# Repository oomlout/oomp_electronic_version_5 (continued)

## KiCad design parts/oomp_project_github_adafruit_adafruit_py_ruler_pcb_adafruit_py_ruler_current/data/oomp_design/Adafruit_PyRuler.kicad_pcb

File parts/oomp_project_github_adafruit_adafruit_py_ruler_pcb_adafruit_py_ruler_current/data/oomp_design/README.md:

# OOMP KiCad design copy

Open `Adafruit_PyRuler.kicad_pro` (or the `.kicad_pcb` / `.kicad_sch`) in KiCad. Local OOMP libraries are under `libraries/`. Original inputs are preserved in [../original/](../original/).

Only verified unchanged installed KiCad defaults were renamed. Modified, custom, unmatched and unavailable items remain unchanged. Soldering variants are never swapped during conversion. Existing pad coordinates, nets and UUIDs are preserved.

See [conversion_report.yaml](conversion_report.yaml) for every conversion and skip. Copy this directory before editing; regeneration refuses to overwrite edited design files.

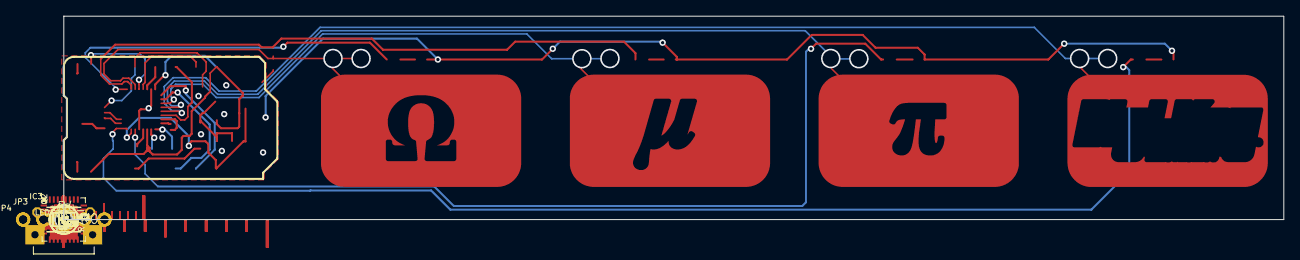
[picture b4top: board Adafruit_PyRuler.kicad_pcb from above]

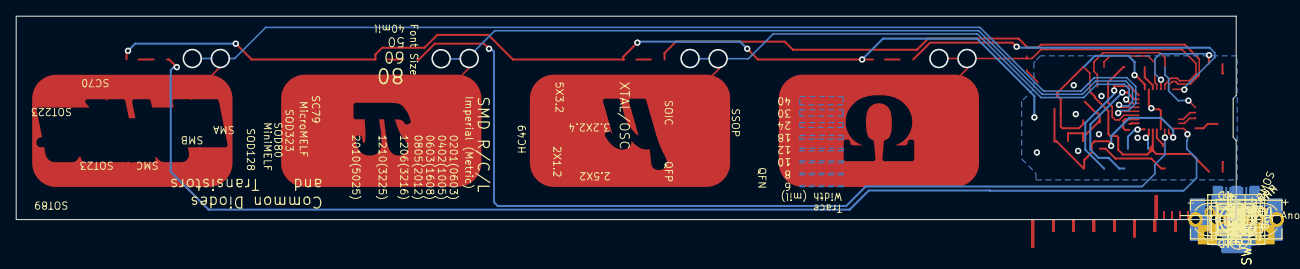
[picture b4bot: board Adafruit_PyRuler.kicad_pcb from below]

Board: 16 copper layers, 152.4 x 25.4 mm, 98 parts (43 on the bottom side), 30 nets.

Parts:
C1, C8: 10uF; 0805-NO
C2, C3: 1uF; 0603-NO
CN1: 4U#20329; 4UCONN_20329_NARROW
D2, D3: SCHOTTKY; SOD-123FL
E$1, E$2, E$3, E$4, E$5, E$6, E$7, E$8, E$9, E$10, E$11, E$12, E$13, E$14, E$15: EDGE-MILLIMETERS
E$16, E$60, E$63: 0201
E$17, E$18, E$19, E$20, E$21, E$22: EDGE-INCHES-TENTH
E$23, E$61: 0402
E$24, E$62: 0603
E$25: 0805
E$26: 1206
E$27: 1210
E$28: 2010
E$31: SOT223
E$32: SOT89
E$33: SOT23-5
E$34: SOT23-3
E$35: SC70
E$36: CRYSTAL-SMD-5X3.2
E$37: CRYSTAL-SMD-3.2X2.5
E$38: CRYSTAL-SMD-2.5X2
E$39: HC49UP
E$40: XTAL-2X1.2
E$41: MICROMELF-R
E$42: SC79_INFINEON
E$43: SMA-DIODE
E$44: SMB-DIODE
E$45: SMC
E$47: SOD-128
E$48: SOD-323
E$49: SOD80C
E$50: NMOS-SYMB
E$51: PMOS-SYMB
E$52: DIODE-SYMB
E$53: LED-GUIDE
E$54: NPN-SYMB
E$55: QFN-24
E$56: TSSOP16
E$57: SO08
E$58: TQFP32-5MM
E$59: PNP-SYMB
IC3: ATSAMD21E; QFN32_5MM
JP3, JP4: 1X05_ROUND_70
L0, L2: red; CHIPLED_0603_NOOUTLINE
L1: yellow; CHIPLED_0603_NOOUTLINE
L3: blue; CHIPLED_0603_NOOUTLINE
L4: green; CHIPLED_0603_NOOUTLINE
LED1: AP102-2020; APA102_2020
PWR0: green; CHIPLED_0603_NOOUTLINE
Q2: reset; BTN_KMR2_4.6X2.8
R1, R2, R3: 2.2K; 0603-NO
R4, R5, R6: 10K; 0603-NO
R7: 2M; 0603-NO
SWC0: TPB1,27; B1,27
SWD0: TPB1,27; B1,27
U1: AP2112K-3.3; SOT23-5
U$1, U$6: FIDUCIAL_1MM
U$2: PYRULER_BOTTOM
U$7: PCBFEAT-REV-040
U$8, U$9: MOUNTINGHOLE2.0; MOUNTINGHOLE_2.0_PLATED
U$14: PYRULER_TOP
U$20: TRINKET_M0_TOP
UNK_HOLE_0: dummyfp0
UNK_HOLE_1: dummyfp1

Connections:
3.3V: C2.1, C8.1, IC3.9, IC3.30, JP4.1, LED1.3, R4.2, U1.5
CAP0: IC3.14, R7.1
D0_A4_PA08_SDA: IC3.11, JP4.4
D1_A0_PA02: IC3.3, JP4.3
D2_A1_PA09_SCL_MISO: IC3.12, JP4.2
D3_A3_PA07_RXD_SCK: IC3.8, JP3.4
D4_A2_PA06_TXD_MOSI: IC3.7, JP3.3
D+: CN1.D+, IC3.24
D-: CN1.D-, IC3.23
DOTSTAR_CLOCK: IC3.2, LED1.5
DOTSTAR_DATA: IC3.1, LED1.6
GND: C1.2, C2.2, C3.2, C8.2, CN1.BASE@1, CN1.BASE@2, CN1.GND, CN1.SPRT@1, CN1.SPRT@2, CN1.SPRT@3, CN1.SPRT@4, IC3.10, IC3.28, IC3.33, JP3.2, L0.C, L1.C, L2.C, L3.C, L4.C, LED1.4, PWR0.C, Q2.B, Q2.B', R7.2, U1.2
LED: IC3.13, R1.2
LED4: IC3.16, R3.2
LED5: IC3.15, R2.2
LED6: IC3.27, R6.2
LED7: IC3.25, R5.2
unnamed: L0.A, R1.1
unnamed: IC3.31, SWC0.TP
unnamed: IC3.32, SWD0.TP
unnamed: PWR0.A, R4.1
unnamed: L1.A, R2.1
unnamed: L2.A, R3.1
unnamed: L4.A, R6.1
unnamed: L3.A, R5.1
VBAT: D3.A, JP3.1
VBUS: CN1.VBUS, D2.A, JP4.5
VDDCORE: C3.1, IC3.29
VOUT: C1.1, D2.C, D3.C, U1.1, U1.3
~RESET: IC3.26, JP3.5, Q2.A, Q2.A'

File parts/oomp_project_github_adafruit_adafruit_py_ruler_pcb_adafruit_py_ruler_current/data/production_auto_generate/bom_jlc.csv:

Comment,Designator,Footprint,LCSC Part #
,"E$16,E$60,E$63",Adafruit_PyRuler-import-fps:0201,
,"E$23,E$61",Adafruit_PyRuler-import-fps:0402,
,"E$24,E$62",Adafruit_PyRuler-import-fps:0603,
,E$25,Adafruit_PyRuler-import-fps:0805,
,E$26,Adafruit_PyRuler-import-fps:1206,
,E$27,Adafruit_PyRuler-import-fps:1210,
,"JP3,JP4",Adafruit_PyRuler-import-fps:1X05_ROUND_70,C42431835
,E$28,Adafruit_PyRuler-import-fps:2010,
,E$38,Adafruit_PyRuler-import-fps:CRYSTAL-SMD-2.5X2,
,E$37,Adafruit_PyRuler-import-fps:CRYSTAL-SMD-3.2X2.5,
,E$36,Adafruit_PyRuler-import-fps:CRYSTAL-SMD-5X3.2,
,E$52,Adafruit_PyRuler-import-fps:DIODE-SYMB,
,"E$17,E$18,E$19,E$20,E$21,E$22",Adafruit_PyRuler-import-fps:EDGE-INCHES-TENTH,
,"E$1,E$2,E$3,E$4,E$5,E$6,E$7,E$8,E$9,E$10,E$11,E$12,E$13,E$14,E$15",Adafruit_PyRuler-import-fps:EDGE-MILLIMETERS,
,E$39,Adafruit_PyRuler-import-fps:HC49UP,
,E$53,Adafruit_PyRuler-import-fps:LED-GUIDE,
,E$41,Adafruit_PyRuler-import-fps:MICROMELF-R,
,E$50,Adafruit_PyRuler-import-fps:NMOS-SYMB,
,E$54,Adafruit_PyRuler-import-fps:NPN-SYMB,
,U$7,Adafruit_PyRuler-import-fps:PCBFEAT-REV-040,
,E$51,Adafruit_PyRuler-import-fps:PMOS-SYMB,
,E$59,Adafruit_PyRuler-import-fps:PNP-SYMB,
,U$2,Adafruit_PyRuler-import-fps:PYRULER_BOTTOM,
,U$14,Adafruit_PyRuler-import-fps:PYRULER_TOP,
,E$55,Adafruit_PyRuler-import-fps:QFN-24,
,E$35,Adafruit_PyRuler-import-fps:SC70,
,E$42,Adafruit_PyRuler-import-fps:SC79_INFINEON,
,E$43,Adafruit_PyRuler-import-fps:SMA-DIODE,
,E$44,Adafruit_PyRuler-import-fps:SMB-DIODE,
,E$45,Adafruit_PyRuler-import-fps:SMC,
,E$57,Adafruit_PyRuler-import-fps:SO08,
,E$47,Adafruit_PyRuler-import-fps:SOD-128,
,E$48,Adafruit_PyRuler-import-fps:SOD-323,
,E$49,Adafruit_PyRuler-import-fps:SOD80C,
,E$31,Adafruit_PyRuler-import-fps:SOT223,
,E$34,Adafruit_PyRuler-import-fps:SOT23-3,
,E$33,Adafruit_PyRuler-import-fps:SOT23-5,
,E$32,Adafruit_PyRuler-import-fps:SOT89,
,E$58,Adafruit_PyRuler-import-fps:TQFP32-5MM,
,U$20,Adafruit_PyRuler-import-fps:TRINKET_M0_TOP,
,E$56,Adafruit_PyRuler-import-fps:TSSOP16,
,E$40,Adafruit_PyRuler-import-fps:XTAL-2X1.2,
10K,"R4,R5,R6",Adafruit_PyRuler-import-fps:0603-NO,C98220
10uF,"C1,C8",Adafruit_PyRuler-import-fps:0805-NO,
1uF,"C2,C3",Adafruit_PyRuler-import-fps:0603-NO,C5673
2.2K,"R1,R2,R3",Adafruit_PyRuler-import-fps:0603-NO,C4190
2M,R7,Adafruit_PyRuler-import-fps:0603-NO,
4U#20329,CN1,Adafruit_PyRuler-import-fps:4UCONN_20329_NARROW,
AP102-2020,LED1,Adafruit_PyRuler-import-fps:APA102_2020,
AP2112K-3.3,U1,Adafruit_PyRuler-import-fps:SOT23-5,
ATSAMD21E,IC3,Adafruit_PyRuler-import-fps:QFN32_5MM,
blue,L3,Adafruit_PyRuler-import-fps:CHIPLED_0603_NOOUTLINE,
FIDUCIAL_1MM,"U$1,U$6",Adafruit_PyRuler-import-fps:FIDUCIAL_1MM,
green,"L4,PWR0",Adafruit_PyRuler-import-fps:CHIPLED_0603_NOOUTLINE,
red,"L0,L2",Adafruit_PyRuler-import-fps:CHIPLED_0603_NOOUTLINE,
reset,Q2,Adafruit_PyRuler-import-fps:BTN_KMR2_4.6X2.8,
SCHOTTKY,"D2,D3",Adafruit_PyRuler-import-fps:SOD-123FL,
"TPB1,27","SWC0,SWD0","Adafruit_PyRuler-import-fps:B1,27",
yellow,L1,Adafruit_PyRuler-import-fps:CHIPLED_0603_NOOUTLINE,
